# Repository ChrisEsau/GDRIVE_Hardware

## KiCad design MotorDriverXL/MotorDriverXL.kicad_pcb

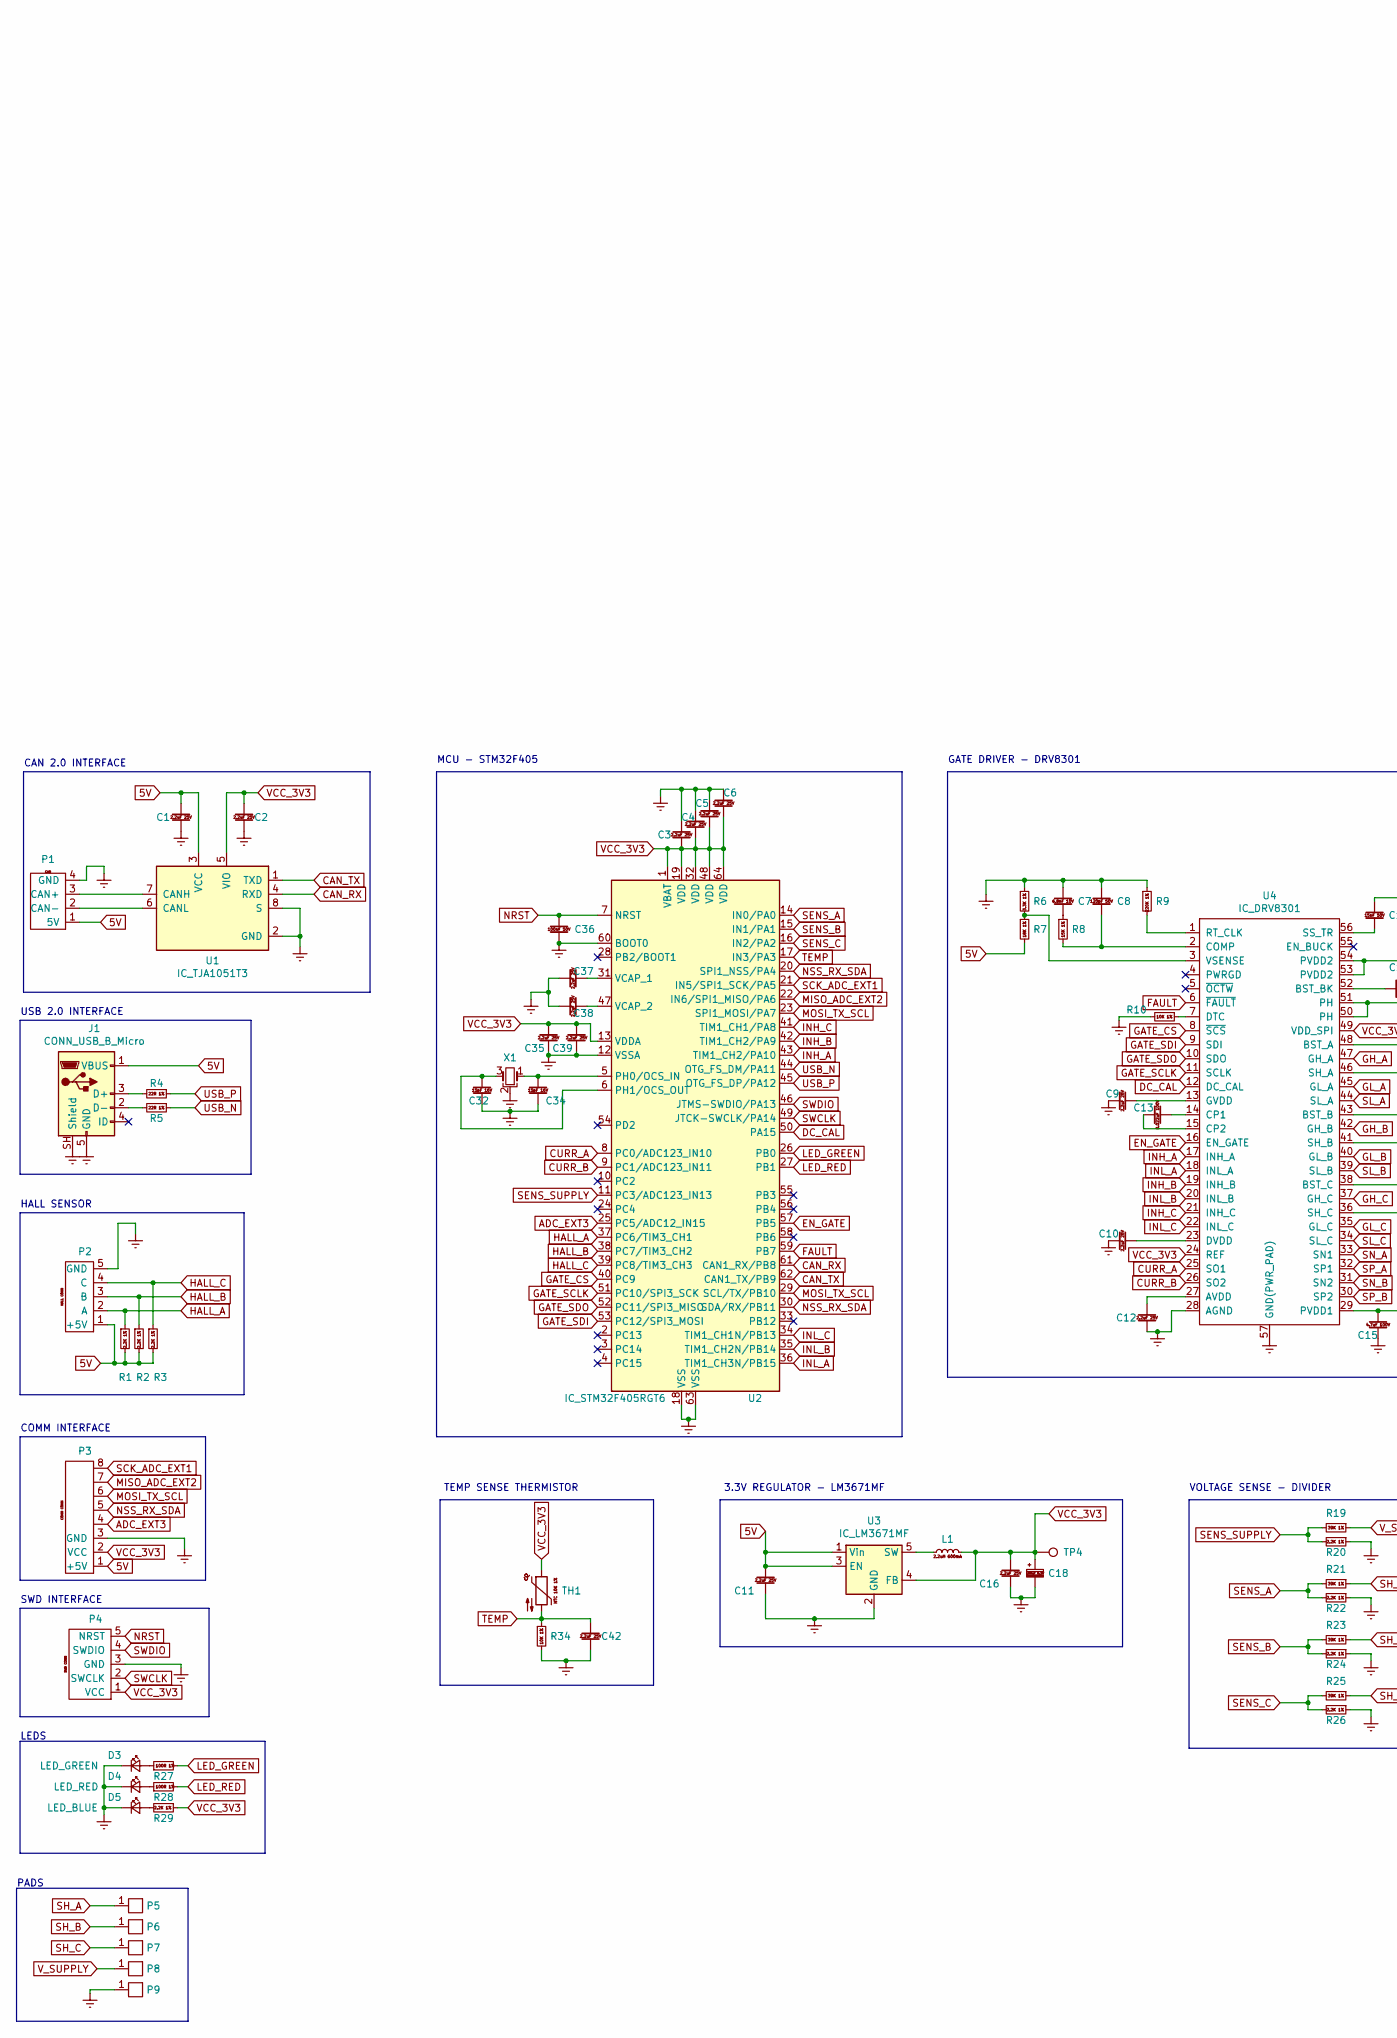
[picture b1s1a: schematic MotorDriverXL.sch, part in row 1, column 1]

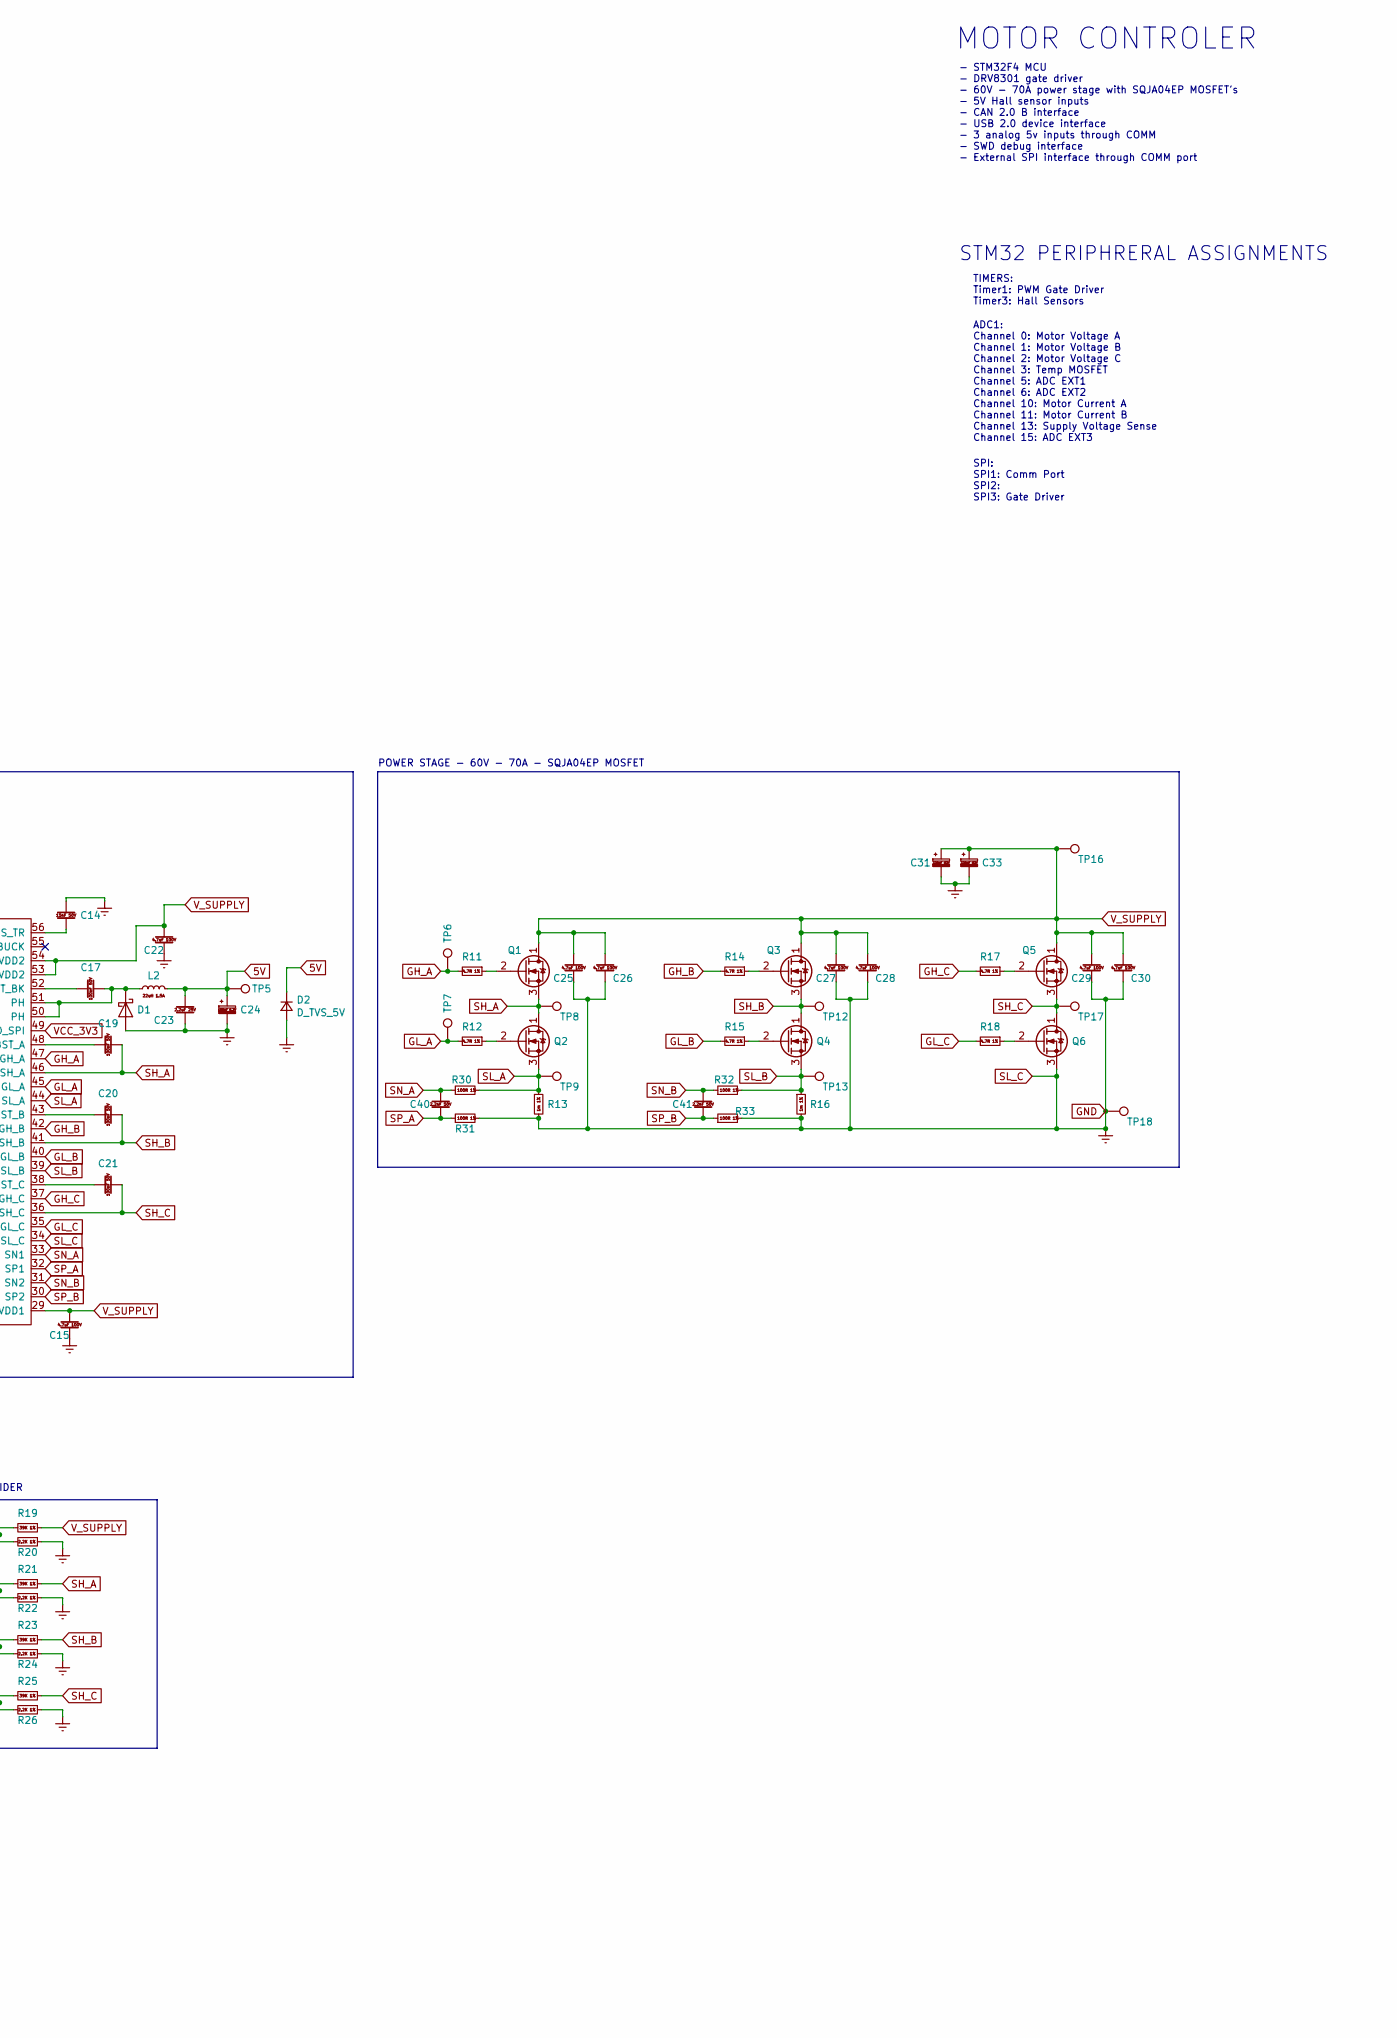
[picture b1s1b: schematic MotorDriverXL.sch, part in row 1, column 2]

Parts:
C1, C2, C3, C4, C5, C6, C9, C10, C11, C12, C16, C23, C35, C37, C38, C39, C42: CAP_2.2uF_25V_0603; C_0603_1608Metric; MPN GRM188R61E225KA12D
C7: CAP_6.8nF_10V_0603; C_0603_1608Metric; MPN VJ0603Y682MXQPW1BC
C8: CAP_120pF_50V_0603; C_0603_1608Metric; MPN VJ0603A121JXAAC
C13: CAP_0.022uF_100V_0603; C_0603_1608Metric; MPN C0603C223K1RACTU
C14: CAP_15nF_50V_0603; C_0603_1608Metric; MPN CC0603JRX7R9BB153
C15, C22, C25, C26, C27, C28, C29, C30: CAP_4.7uF_100V_1210; C_1210_3225Metric; MPN GCM32DC72A475KE02L
C17, C19, C20, C21, C36: CAP_100nF_50V_0603; C_0603_1608Metric; MPN CC0603MRY5V9BB104
C18, C24: CAPP_100uF_6.3V_TANT; C_1210_3225Metric; MPN 581-TPSB107K006R0400
C31, C33: CAPP_220uF_63V_10X15_THT; CP_Radial_D10.0mm_P5.00mm; MPN ESK227M063AH2AA
C32, C34: CAP_15pF_16V_0603; C_0603_1608Metric; MPN VJ0603A150KXJPW1BC
C40, C41: CAP_2.2nF_50V_0603; C_0603_1608Metric; MPN C0603C222J5RACTU
D1: D_60V_2A_PMEG6020ER; D_SOD-123F; MPN PMEG6020ER
D2: D_TVS_5V; DO-214AC
D3: LED_GREEN; LED_0603_1608Metric; MPN LTST-C191KGKT
D4: LED_RED; LED_0603_1608Metric; MPN LTST-C191KRKT
D5: LED_BLUE; LED_0603_1608Metric; MPN LTST-C191TBKT
J1: CONN_USB_B_Micro; USB_Micro_B_Female_10118193-0001LF; MPN 10118193-0001LF
L1: L_2.2uH_600mA_MLZ2012N2R2L; L_0805_2012Metric; MPN MLZ2012N2R2L
L2: L_22uH_1.5A_SDR0805; L_BOURNS_SDR0805; MPN 652-SDR0805-220ML
P1: CONN_CAN; PinHeader_1x04_P2.54mm_Vertical; MPN 90136-1104
P2: CONN_HALL; PinHeader_1x05_P2.54mm_Vertical; MPN 90136-1305
P3: CONN_COMM; PinHeader_1x08_P2.54mm_Vertical; MPN 90136-1108
P4: CONN_SWD; PinHeader_1x05_P2.54mm_Vertical; MPN 90136-1305
P5, P6, P7, P8, P9: PAD_4x5
Q1, Q2, Q3, Q4, Q5, Q6: Q_NMOS_60V_70A; POWERPAK SO-8L SINGLE; MPN SQJA04EP-T1_GE3
R1, R2, R3, R20, R22, R24, R26, R29: RES_2.2K_1%_0603; R_0603_1608Metric; MPN RC0603JR-072K2L
R4, R5: RES_22R_1%_0603; R_0603_1608Metric; MPN RC0603FR-0722RL
R6: RES_3.3K_1%_0603; R_0603_1608Metric; MPN RC0603FR-073K3L
R7: RES_18K_1%_0603; R_0603_1608Metric; MPN RC0603FR-0718KL
R8: RES_15K_1%_0603; R_0603_1608Metric; MPN RC0603FR-0715KL
R9: RES_220K_1%_0603; R_0603_1608Metric; MPN RC0603FR-07220KL
R10, R34: RES_10K_1%_0603; R_0603_1608Metric; MPN RC0603FR-0710KL
R11, R12, R14, R15, R17, R18: RES_4.7R_1%_0603; R_0603_1608Metric; MPN RK73H1JTTD4R70F
R13, R16: RES_1m_1%_SHUNT; R_2512_6332Metric; MPN WSLF25121L000FEA
R19, R21, R23, R25: RES_39K_1%_0603; R_0603_1608Metric; MPN RC0603FR-0739KL
R27, R28, R30, R31, R32, R33: RES_100R_1%_0603; R_0603_1608Metric; MPN RC0603FR-07100RL
TH1: TH_NTC_10K_1%_0603; R_0603_1608Metric; MPN NCP18XH103F03RB
TP4, TP5, TP6, TP7, TP8, TP9, TP12, TP13, TP16, TP17, TP18: TestPoint; TestPoint_Pad_2.0x2.0mm
U1: IC_TJA1051T3; SO-8_5.3x6.2mm_P1.27mm; MPN TJA1051T/3,118
U2: IC_STM32F405RGT6; LQFP-64_10x10mm_P0.5mm; MPN STM32F405RGT6
U3: IC_LM3671MF; TSOT-23-5; MPN LM3671MF-1.8/NOPB
U4: IC_DRV8301; HTSSOP-56-1EP_6.1x14mm_P0.5mm_EP3.61x6.35mm; MPN DRV8301DCAR
X1: XTAL_8Mhz_ABM3B; Crystal_SMD_Abracon_ABM3B-4Pin_5.0x3.2mm; MPN 815-ABM3B-8.0-10-1UT

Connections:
5V: C1.2, C11.2, C23.2, C24.1, D2.K, J1.1 (VBUS), L2.2, P1.1 (5V), P2.1 (+5V), P3.1 (+5V), R1.2, R2.2, R3.2, R7.2, TP5.1, U1.3 (VCC), U3.1 (Vin), U3.3 (EN)
ADC_EXT3: P3.4, U2.25 (PC5/ADC12_IN15)
CAN_RX: U1.4 (RXD), U2.61 (CAN1_RX/PB8)
CAN_TX: U1.1 (TXD), U2.62 (CAN1_TX/PB9)
CURR_A: U2.8 (PC0/ADC123_IN10), U4.25 (SO1)
CURR_B: U2.9 (PC1/ADC123_IN11), U4.26 (SO2)
DC_CAL: U2.50 (PA15), U4.12 (DC_CAL)
EN_GATE: U2.57 (PB5), U4.16 (EN_GATE)
FAULT: U2.59 (PB7), U4.6 (~FAULT)
GATE_CS: U2.40 (PC9), U4.8 (~SCS)
GATE_SCLK: U2.51 (PC10/SPI3_SCK), U4.11 (SCLK)
GATE_SDI: U2.53 (PC12/SPI3_MOSI), U4.9 (SDI)
GATE_SDO: U2.52 (PC11/SPI3_MISO), U4.10 (SDO)
GH_A: R11.2, TP6.1, U4.47 (GH_A)
GH_B: R14.2, U4.42 (GH_B)
GH_C: R17.2, U4.37 (GH_C)
GL_A: R12.2, TP7.1, U4.45 (GL_A)
GL_B: R15.2, U4.40 (GL_B)
GL_C: R18.2, U4.35 (GL_C)
GND: C1.1, C2.1, C3.1, C4.2, C5.2, C6.2, C7.1, C8.1, C9.2, C10.2, C11.1, C12.2, C14.1, C15.2, C16.1, C18.2, C22.2, C23.1, C24.2, C25.2, C26.2, C27.2, C28.2, C29.2, C30.2, C31.2, C32.2, C33.2, C34.2, C35.1, C36.2, C37.2, C38.2, C39.1, C42.1, D1.2 (A), D2.A, D3.1 (K), D4.1 (K), D5.1 (K), J1.5 (GND), J1.SH (Shield), P1.4 (GND), P2.5 (GND), P3.3 (GND), P4.3 (GND), P9.1, Q6.3 (S), R6.1, R9.1, R10.2, R13.2, R16.2, R20.1, R22.1, R24.1, R26.1, R31.2, R33.2, R34.2, TP18.1, U1.2 (GND), U1.8 (S), U2.12 (VSSA), U2.18 (VSS), U2.60 (BOOT0), U2.63 (VSS), U3.2 (GND), U4.28 (AGND), U4.34 (SL_C), U4.57 (GND(PWR_PAD)), X1.2
HALL_A: P2.2 (A), R1.1, U2.37 (PC6/TIM3_CH1)
HALL_B: P2.3 (B), R2.1, U2.38 (PC7/TIM3_CH2)
HALL_C: P2.4 (C), R3.1, U2.39 (PC8/TIM3_CH3)
INH_A: U2.43 (TIM1_CH2/PA10), U4.17 (INH_A)
INH_B: U2.42 (TIM1_CH2/PA9), U4.19 (INH_B)
INH_C: U2.41 (TIM1_CH1/PA8), U4.21 (INH_C)
INL_A: U2.36 (TIM1_CH3N/PB15), U4.18 (INL_A)
INL_B: U2.35 (TIM1_CH2N/PB14), U4.20 (INL_B)
INL_C: U2.34 (TIM1_CH1N/PB13), U4.22 (INL_C)
LED_GREEN: R27.2, U2.26 (PB0)
LED_RED: R28.2, U2.27 (PB1)
MISO_ADC_EXT2: P3.7, U2.22 (IN6/SPI1_MISO/PA6)
MOSI_TX_SCL: P3.6, U2.23 (SPI1_MOSI/PA7), U2.29 (SCL/TX/PB10)
NRST: C36.1, P4.5 (NRST), U2.7 (NRST)
NSS_RX_SDA: P3.5, U2.20 (SPI1_NSS/PA4), U2.30 (SDA/RX/PB11)
unnamed: C7.2, R8.1
unnamed: C8.2, R8.2, U4.2 (COMP)
unnamed: C9.1, U4.13 (GVDD)
unnamed: C10.1, U4.23 (DVDD)
unnamed: C12.1, U4.27 (AVDD)
unnamed: C13.1, U4.14 (CP1)
unnamed: C13.2, U4.15 (CP2)
unnamed: C14.2, U4.56 (SS_TR)
unnamed: C17.1, D1.1 (K), L2.1, U4.50 (PH), U4.51 (PH)
unnamed: C17.2, U4.52 (BST_BK)
unnamed: C19.2, U4.48 (BST_A)
unnamed: C20.2, U4.43 (BST_B)
unnamed: C21.2, U4.38 (BST_C)
unnamed: C32.1, U2.6 (PH1/OCS_OUT), X1.3
unnamed: C34.1, U2.5 (PH0/OCS_IN), X1.1
unnamed: C37.1, U2.31 (VCAP_1)
unnamed: C38.1, U2.47 (VCAP_2)
unnamed: D3.2 (A), R27.1
unnamed: D4.2 (A), R28.1
unnamed: D5.2 (A), R29.2
unnamed: J1.2 (D-), R5.2
unnamed: J1.3 (D+), R4.2
unnamed: L1.1, U3.5 (SW)
unnamed: P1.2 (CAN-), U1.6 (CANL)
unnamed: P1.3 (CAN+), U1.7 (CANH)
unnamed: Q1.2 (G), R11.1
unnamed: Q2.2 (G), R12.1
unnamed: Q3.2 (G), R14.1
unnamed: Q4.2 (G), R15.1
unnamed: Q5.2 (G), R17.1
unnamed: Q6.2 (G), R18.1
unnamed: R6.2, R7.1, U4.3 (VSENSE)
unnamed: R9.2, U4.1 (RT_CLK)
unnamed: R10.1, U4.7 (DTC)
SCK_ADC_EXT1: P3.8, U2.21 (IN5/SPI1_SCK/PA5)
SENS_A: R21.2, R22.2, U2.14 (IN0/PA0)
SENS_B: R23.2, R24.2, U2.15 (IN1/PA1)
SENS_C: R25.2, R26.2, U2.16 (IN2/PA2)
SENS_SUPPLY: R19.2, R20.2, U2.11 (PC3/ADC123_IN13)
SH_A: C19.1, P5.1, Q1.3 (S), Q2.1 (D), R21.1, TP8.1, U4.46 (SH_A)
SH_B: C20.1, P6.1, Q3.3 (S), Q4.1 (D), R23.1, TP12.1, U4.41 (SH_B)
SH_C: C21.1, P7.1, Q5.3 (S), Q6.1 (D), R25.1, TP17.1, U4.36 (SH_C)
SL_A: Q2.3 (S), R13.1, R30.2, TP9.1, U4.44 (SL_A)
SL_B: Q4.3 (S), R16.1, R32.2, TP13.1, U4.39 (SL_B)
SN_A: C40.1, R30.1, U4.33 (SN1)
SN_B: C41.1, R32.1, U4.31 (SN2)
SP_A: C40.2, R31.1, U4.32 (SP1)
SP_B: C41.2, R33.1, U4.30 (SP2)
SWCLK: P4.2 (SWCLK), U2.49 (JTCK-SWCLK/PA14)
SWDIO: P4.4 (SWDIO), U2.46 (JTMS-SWDIO/PA13)
TEMP: C42.2, R34.1, TH1.2, U2.17 (IN3/PA3)
USB_N: R5.1, U2.44 (OTG_FS_DM/PA11)
USB_P: R4.1, U2.45 (OTG_FS_DP/PA12)
VCC_3V3: C2.2, C3.2, C4.1, C5.1, C6.1, C16.2, C18.1, C35.2, C39.2, L1.2, P3.2 (VCC), P4.1 (VCC), R29.1, TH1.1, TP4.1, U1.5 (VIO), U2.1 (VBAT), U2.13 (VDDA), U2.19 (VDD), U2.32 (VDD), U2.48 (VDD), U2.64 (VDD), U3.4 (FB), U4.24 (REF), U4.49 (VDD_SPI)
V_SUPPLY: C15.1, C22.1, C25.1, C26.1, C27.1, C28.1, C29.1, C30.1, C31.1, C33.1, P8.1, Q1.1 (D), Q3.1 (D), Q5.1 (D), R19.1, TP16.1, U4.29 (PVDD1), U4.53 (PVDD2), U4.54 (PVDD2)

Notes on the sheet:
TIMERS: Timer1: PWM Gate Driver Timer3: Hall Sensors
ADC1: Channel 0: Motor Voltage A Channel 1: Motor Voltage B Channel 2: Motor Voltage C Channel 3: Temp MOSFET Channel 5: ADC EXT1 Channel 6: ADC EXT2 Channel 10: Motor Current A Channel 11: Motor Current B Channel 13: Supply Voltage Sense Channel 15: ADC EXT3
SPI: SPI1: Comm Port SPI2: SPI3: Gate Driver
PADS
LEDS
SWD INTERFACE
COMM INTERFACE
HALL SENSOR
USB 2.0 INTERFACE
CAN 2.0 INTERFACE
MCU - STM32F405
GATE DRIVER - DRV8301
3.3V REGULATOR - LM3671MF
POWER STAGE - 60V - 70A - SQJA04EP MOSFET
TEMP SENSE THERMISTOR
VOLTAGE SENSE - DIVIDER
MOTOR CONTROLER
- STM32F4 MCU - DRV8301 gate driver - 60V - 70A power stage with SQJA04EP MOSFET's - 5V Hall sensor inputs - CAN 2.0 B interface - USB 2.0 device interface - 3 analog 5v inputs through COMM - SWD debug interface - External SPI interface through COMM port
STM32 PERIPHRERAL ASSIGNMENTS

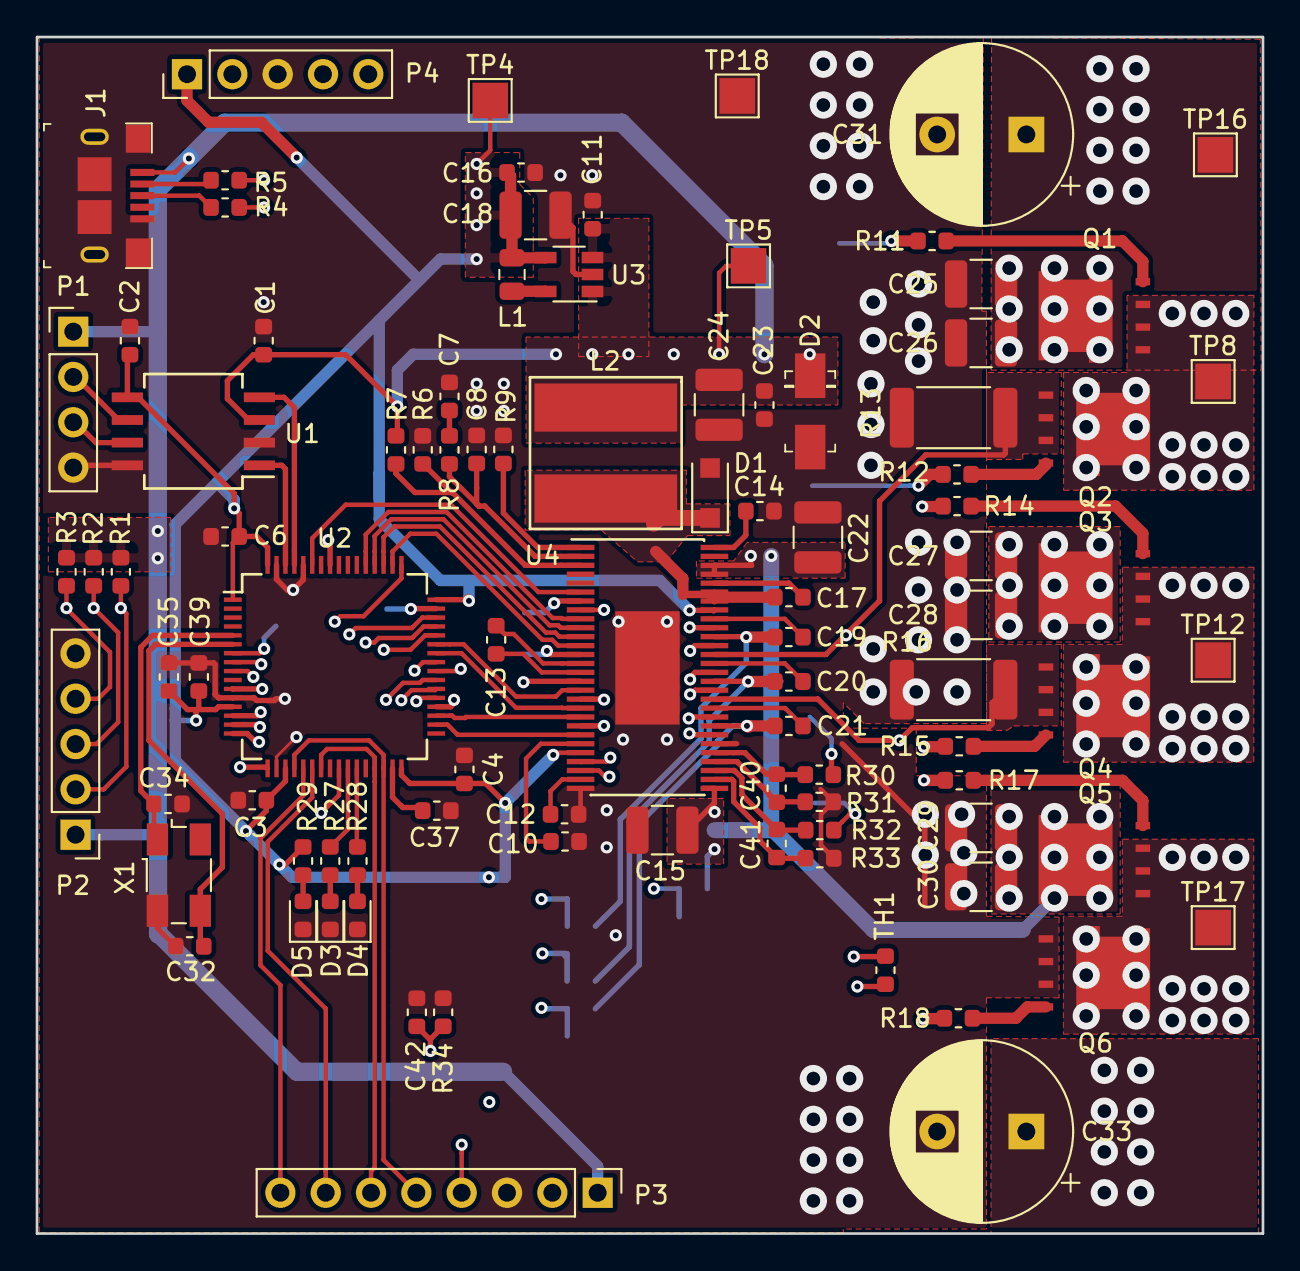
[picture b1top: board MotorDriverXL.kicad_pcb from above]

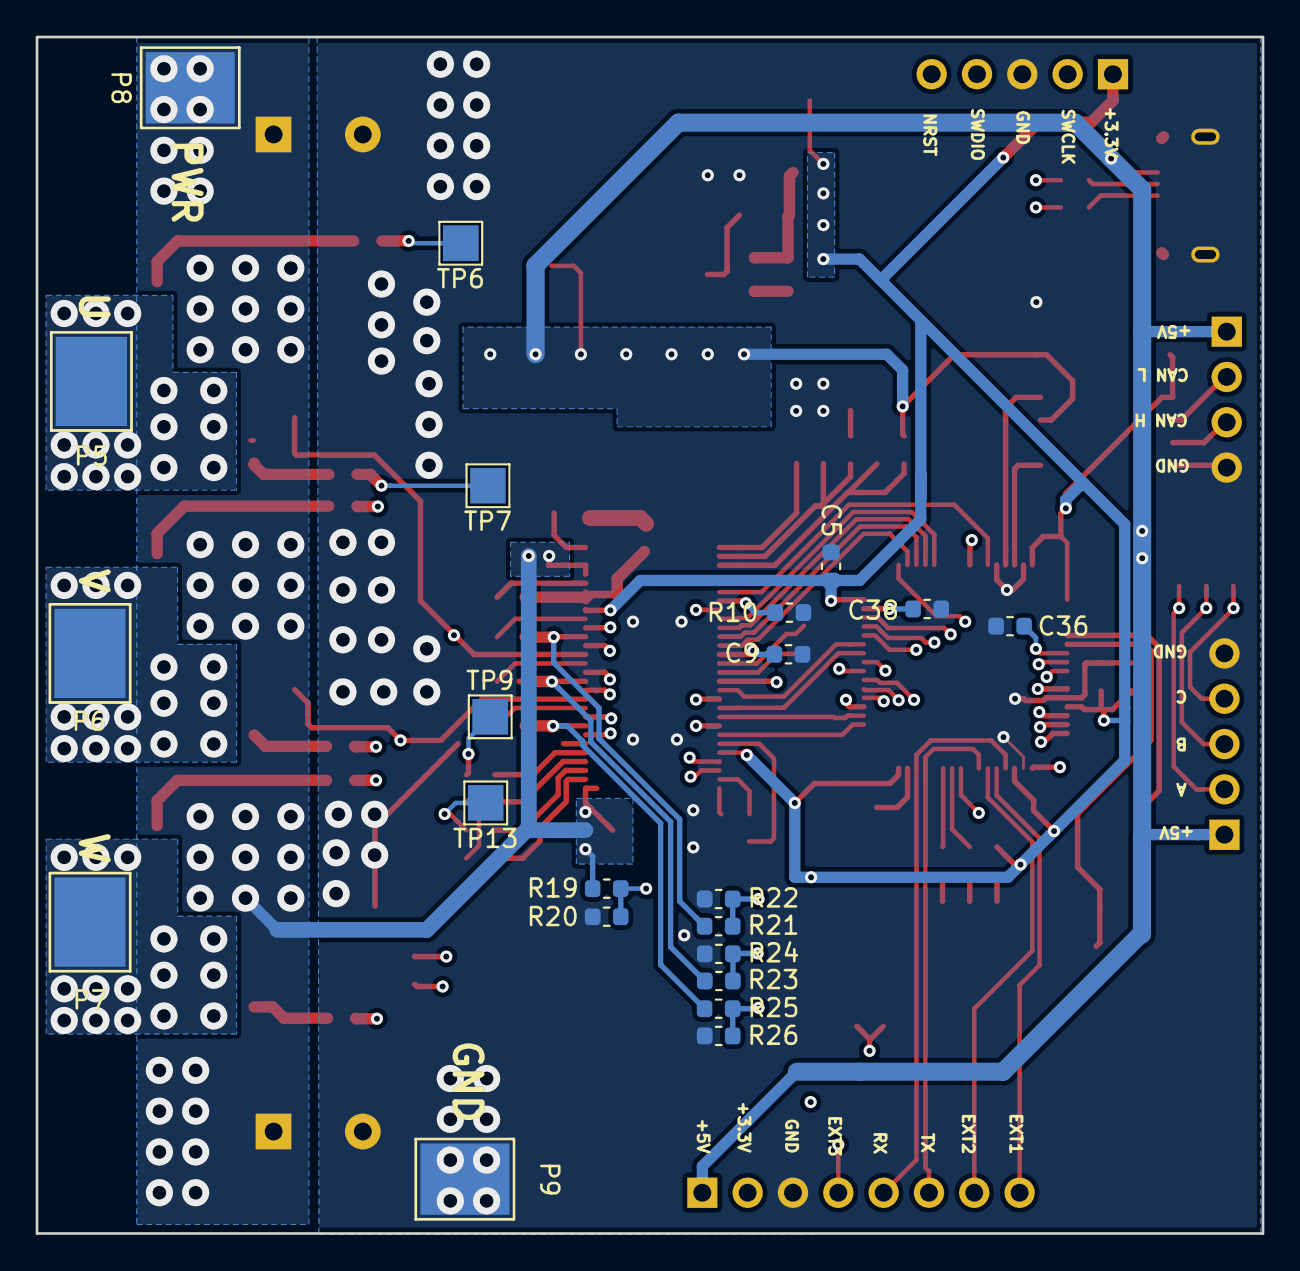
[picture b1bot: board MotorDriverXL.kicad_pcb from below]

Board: 4 copper layers, 68.7 x 67.1 mm, 116 parts (22 on the bottom side), 90 nets.
